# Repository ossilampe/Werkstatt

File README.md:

# Werkstatt

Eigene Geräte und Platinen für die Werkstatt, mit Schaltplan, Platinendaten und Firmware.

| Projekt | Hardware | Wofür | Stand |
|---|---|---|---|
| [T12-Station-2-Kolben](T12-Station-2-Kolben) | Waveshare ESP32-S3 Touch-LCD 3,5″ + 2 × fertige T12-Steuerplatine (STM32 Ver21S) mit eigener UART-Firmware | Lötstation für 2 T12-Kolben: Touch + Drehgeber, Spitzenprofile aus Home Assistant, Sprachausgabe, Lüfter, Absaugung | läuft im 3D-Druck-Gehäuse (mit 1 Modul getestet), Absaugung folgt |
| [T12-Station-1-Kolben](T12-Station-1-Kolben) | wie oben, 1 × T12-Steuerplatine | dieselbe Station für einen Kolben | Konfiguration fertig, Gehäuse wie 2 Kolben |
| [T12-Loetstation](T12-Loetstation) | Waveshare ESP32-S3 Touch-LCD 3,5″ + eigene Platine (KiCad, JLCPCB) | erster Entwurf mit eigener Platine für 2 Kolben | Platine v1.1 fertig, pausiert |
| [E-Last-ZHIYU-ESP32](E-Last-ZHIYU-ESP32) | Elektronische Last ZHIYU ZPB30A1 (60 W) mit freier Firmware + Waveshare ESP32-S3 Touch-LCD 3,5″ | Last per Display und Home Assistant steuern; geplant: Akkutest, Rampentest mit Protokoll | geflasht, Display zeigt Live-Daten; Befehle und Kalibrierung offen |
| [Labornetzteil-XY6020L](Labornetzteil-XY6020L) | 60-V/20-A-Netzteil + XY6020L (Modbus) + Waveshare ESP32-S3 Touch-LCD 3,5″ | Labornetzteil 0–60 V / 0–20 A mit Touch, Schutzgrenzen, Home Assistant | Entwurf: Konfiguration v1 geschrieben, noch nicht aufgebaut |
| [Mikroskop](Mikroskop) | Raspberry Pi 4 + HQ-Kamera + offizielles 7″-Touchdisplay + 4 Taster | Digitales Mikroskop: Zoom bis 8×, Verschieben per Wischen, Bild-Einstellungen, Foto auf SMB-Freigabe | App geschrieben, auf echter Hardware noch nicht getestet |

**Gehäuse der T12-Station zum Drucken:** [MakerWorld](https://makerworld.com/de/models/3663781-t12-lotstation-esp32-s3-touch-display-2-kolben)

**Hinweis:** WLAN-Daten und Passwörter kommen per `!secret` aus der eigenen `secrets.yaml`. Eine Vorlage liegt jeweils als `secrets.yaml.example` im Projektordner.

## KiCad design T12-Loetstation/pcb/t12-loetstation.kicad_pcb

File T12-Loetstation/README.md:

# T12 Lötstation – 2 Kolben gleichzeitig

Selbstgebaute Lötstation für **zwei T12-Lötspitzen gleichzeitig**, mit eigenem Touch-Display, Drehgeber, Lüftersteuerung, Anschluss für eine Lötrauch-Absaugung und Sprachausgabe.

> **Stand 13.11.2026: pausiert.** Die Platine (v1.1) ist fertig geprüft und bei JLCPCB bestellbar, aber noch nicht bestellt. Die Firmware ist ein Entwurf (noch nicht kompiliert, Lüfter/Absaugung/Ton fehlen).

## So soll es aussehen

Display: Waveshare ESP32-S3-Touch-LCD-3.5 quer (480 × 320), ESPHome + LVGL. Bedienung per Touch oder Drehgeber (drehen = Temperatur, langer Druck = Menü).

| | |
|---|---|
|  |  |
|  |  |
|  |  |
|  | |

Die Bilder werden mit [`docs/gen_menues.py`](docs/gen_menues.py) erzeugt (Maße und Farben wie in der Firmware). „Geplant“ heißt: in der Firmware noch nicht umgesetzt.

**Zustände pro Kolben:** AUS · HEIZT (orange) · BEREIT (grün) · KÜHLT AB · STANDBY (blau, Kolben in der Ablage) · SCHLÄFT · KEINE SPITZE (gelb) · Fehler Übertemperatur / heizt nicht / Messung (rot).

## Funktionen

- 2 × T12 an 24 V (je ca. 70 W), jede Spitze eigene Solltemperatur, Festwerte 280 / 330 / 380 °C
- Temperaturmessung im Heizpausen-Fenster: Auto-Zero-Verstärker MCP6V27 (× 221) → 16-Bit-ADC ADS1115, Kaltstelle MCP9700
- Standby und Schlafen über den Neigungsschalter im Griff, Erkennung „keine Spitze“
- Nach Stromausfall bleiben beide Kolben **aus**
- Netzteil-Lüfter 12 V, temperaturgeregelt über DS18B20
- Buchse vorne (Cinch) für eine 12-V-Absaugung: Drehzahl am Display, schaltet sich ein, wenn ein Kolben in die Hand genommen wird, 10 s Nachlauf
- Pieptöne und deutsche Sprachansagen über den Lautsprecher des Displays (ES8311)

## Hardware

| Teil | |
|---|---|
| Display | Waveshare ESP32-S3-Touch-LCD-3.5 |
| Netzteil | 24 V / 10 A |
| Spannungen | 2 × LM2596-Modul (5 V Display, 12 V Lüfter) per Kabel, AMS1117-3.3 für die Analogseite |
| Heizung | IRF5305 (P-Kanal, Plus-Seite) mit MMBT3904-Treiber, je Kolben eine Sicherung im Gehäuse |
| Bedienung | Drehgeber ALPS STEC12E08 |
| Lüfter | 2 × AO3400A mit 25 kHz PWM |

### GPIO-Belegung (Stiftleiste des Displays)

| GPIO | Funktion | | GPIO | Funktion |
|---|---|---|---|---|
| 38 | Heizung A | | 17 | Griffschalter A |
| 39 | Heizung B | | 18 | Griffschalter B |
| 40 / 41 | Drehgeber A / B | | 21 | DS18B20 |
| 42 | Drehgeber Taster | | 47 | Netzteil-Lüfter (PWM) |
| 8 / 7 | I²C SDA / SCL (ADS1115 0x48) | | 48 | Absaugung (PWM) |

## Platine

150 × 105 mm, 2 Lagen, vollständig bedruckt. Alle Klemmen und Buchsen sind mit Signal und GPIO beschriftet.

- **Schaltplan:** [pcb/t12-schaltplan.pdf](pcb/t12-schaltplan.pdf)
- **KiCad 10:** `pcb/t12-loetstation.kicad_pro`
- **Bestellung bei JLCPCB:** [pcb/jlc/ANLEITUNG.md](pcb/jlc/ANLEITUNG.md)
  - Gerber, Stückliste mit LCSC-Nummern (21 Positionen, nur SMD) und Bestückungsdatei liegen bereit.
  - Die Drehungen sind in der JLC-Vorschau kontrolliert.
- **Selbst löten:** die bedrahteten Teile ([pcb/jlc/Selbst_loeten.csv](pcb/jlc/Selbst_loeten.csv)): Schraubklemmen, JST-XH-Buchsen, IRF5305, Elkos, MCP9700, Sicherungshalter.

Die Platine wird komplett aus Python erzeugt (mit dem Python von KiCad aufrufen, im Ordner `pcb`):

```
design.py    Bauteile und Netze (eine Quelle für alles)
gen_sch.py   -> Schaltplan
gen_pcb.py   -> Platzierung, Bedruckung, Leiterbahnklassen
route.py     -> Freerouting (export / run / import), Masseflächen
make_jlc.py  -> Gerber-Zip, BOM, CPL für JLCPCB
```

### Änderungen v1.1 (Durchsicht vor der Bestellung)
- 1-MΩ-Pull-up (Erkennung „keine Spitze“) an die Spitze verlegt. Vorher hätte er den Messverstärker übersteuert.
- Filter am Messeingang 10 nF → 1 nF: schwingt nach dem Abschalten der Heizung in unter 1 ms ein.
- Massepads der Klemmen J1–J3 vollflächig an die Massefläche (2 × 3 A Heizstrom).
- Drehung der SS14-Dioden in der Bestückungsdatei korrigiert.

## Firmware

[`firmware/t12-loetstation.yaml`](firmware/t12-loetstation.yaml) + [`firmware/t12/loet.h`](firmware/t12/loet.h) (Regler, Zustände).

- **Regelung:** alle 100 ms. Beide Heizungen kurz aus, 3 ms warten, ADS1115 lesen, dann PI-Regler je Kolben.
- **Sicherheit:** über 480 °C, Spitze fehlt oder kein Temperaturanstieg in 20 s → Heizung aus.
- **WLAN-Daten:** per `!secret`, Vorlage in [`firmware/secrets.yaml.example`](firmware/secrets.yaml.example).

**Offen:**
- Lüfter, DS18B20, Absaugung
- Ton und Sprachausgabe
- Menüseiten 03, 05, 06
- Schalter auf `ALWAYS_OFF`
- Kalibrierung mit Spitzenthermometer
- Griffbelegung und Neigungsschalter nachmessen

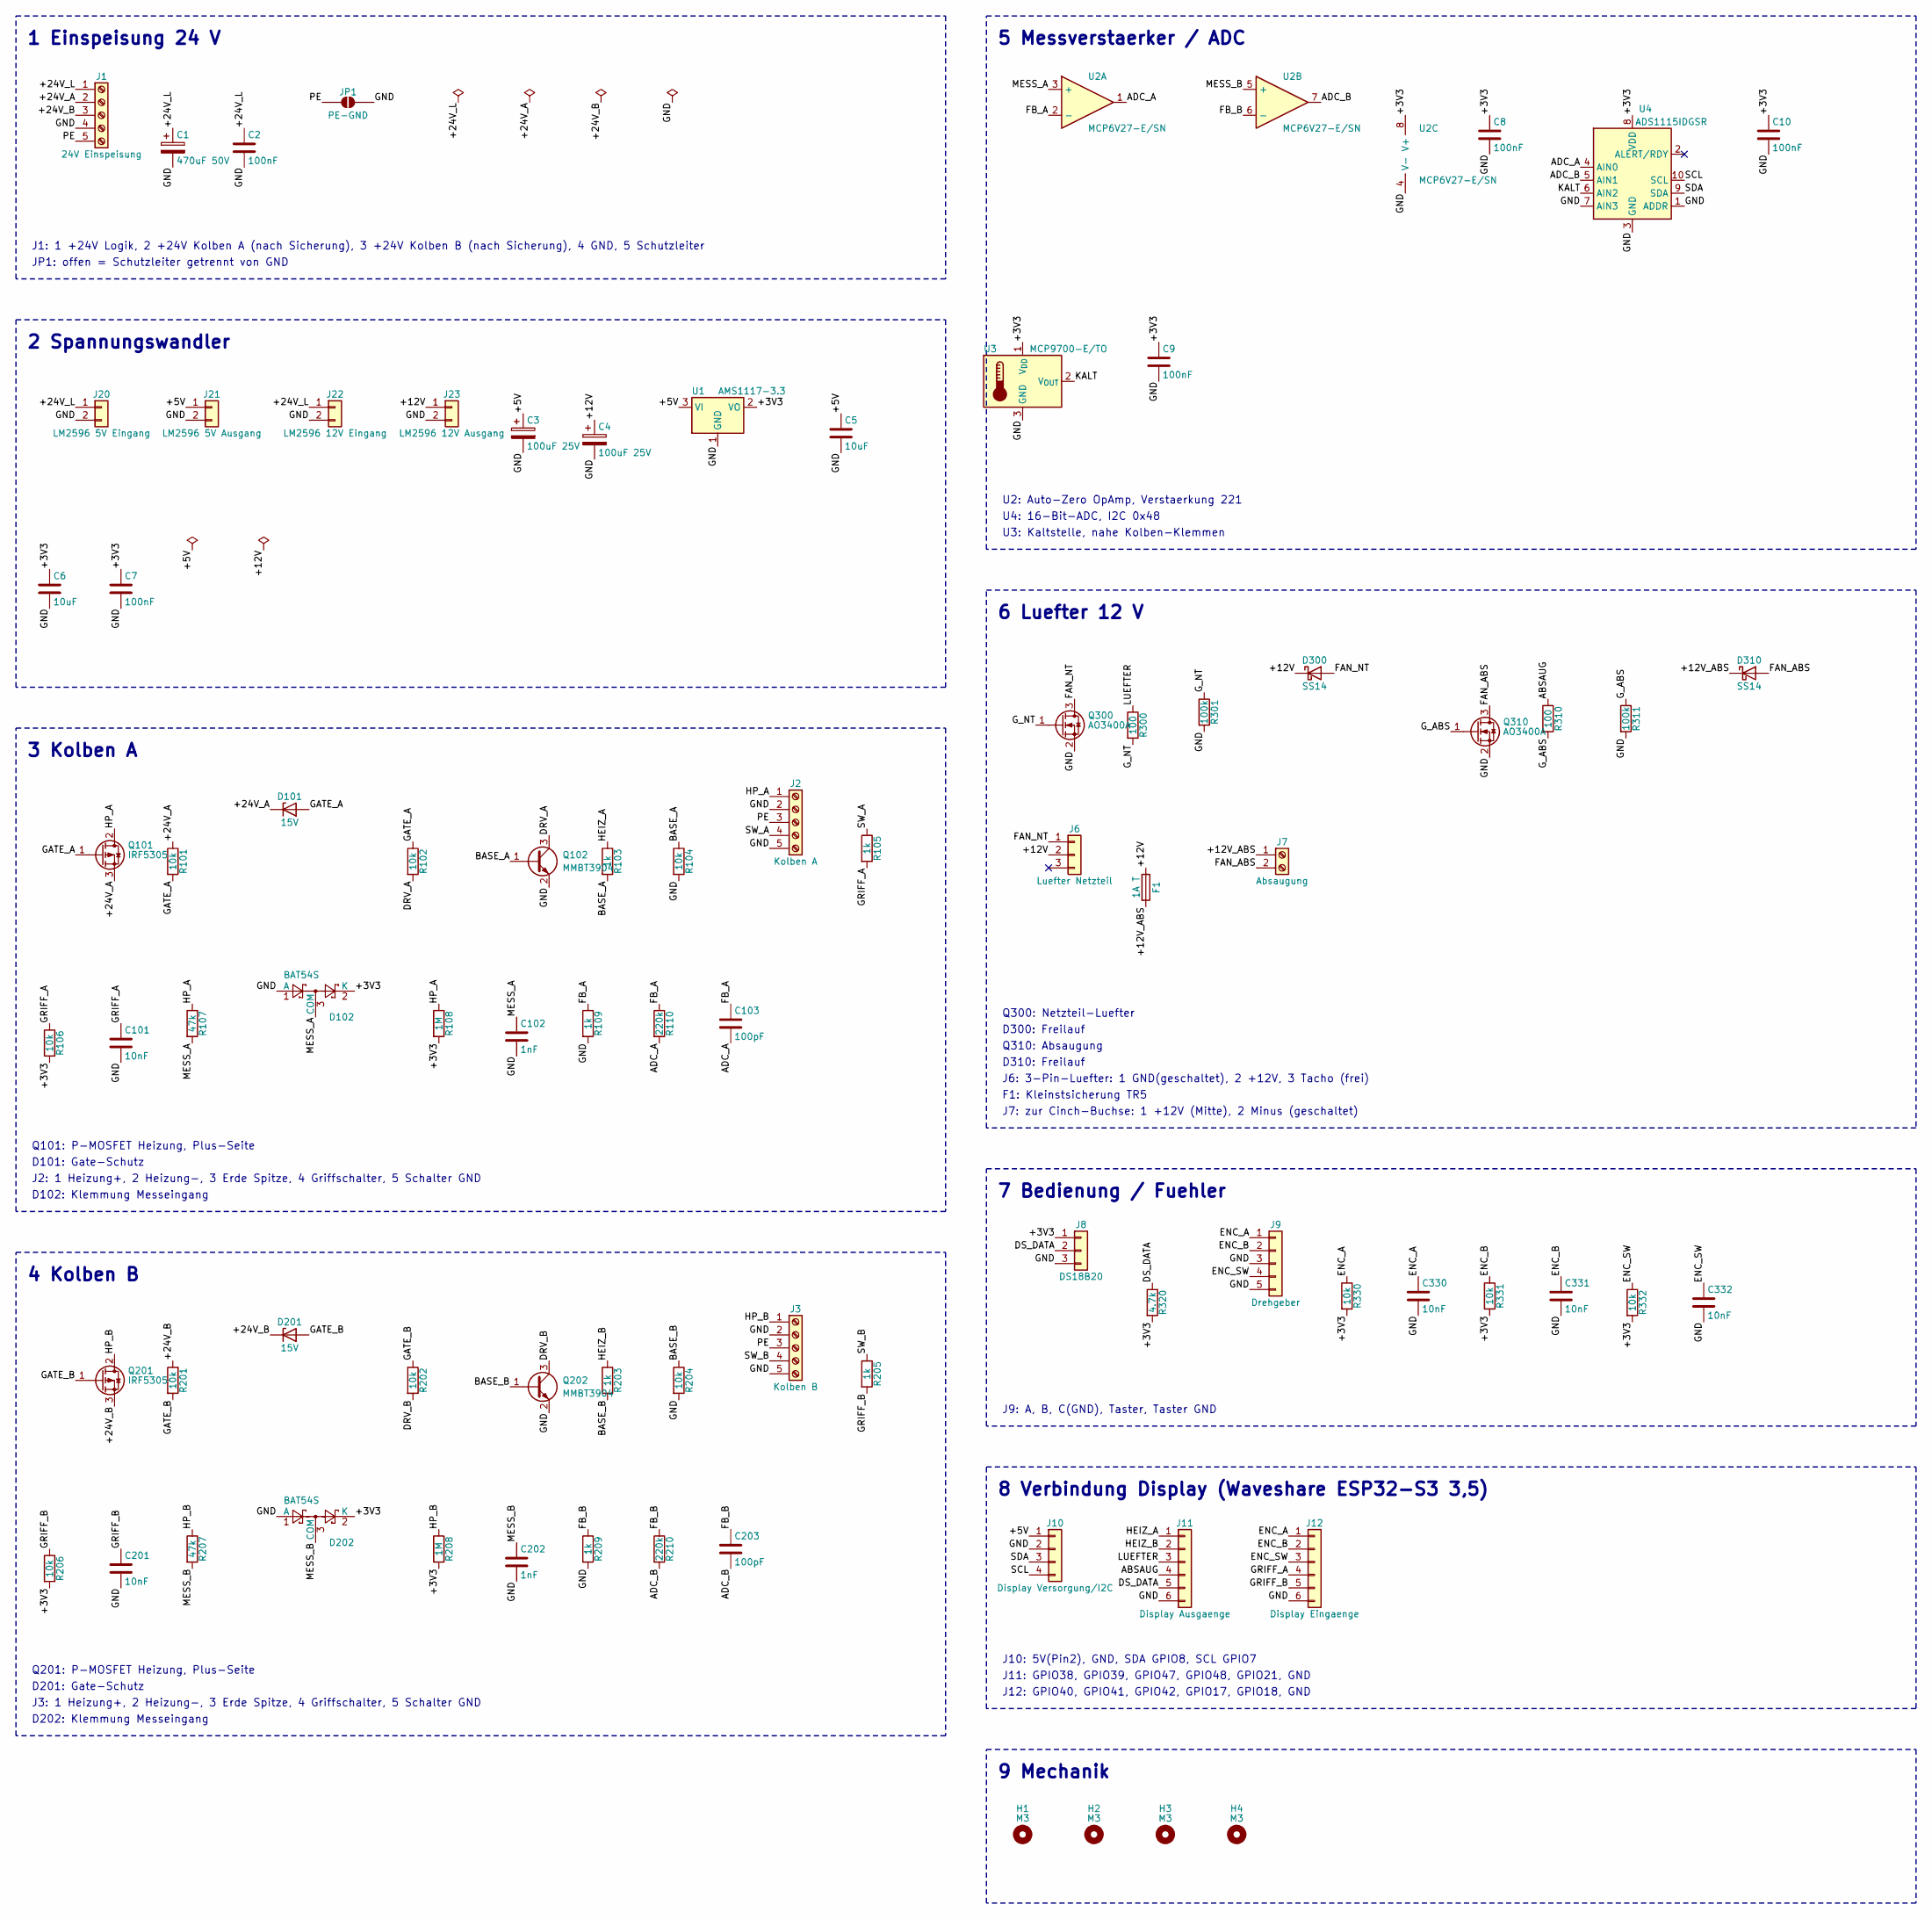
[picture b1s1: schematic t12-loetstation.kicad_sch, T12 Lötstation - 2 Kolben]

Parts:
C1: 470uF 50V; CP_Radial_D10.0mm_P5.00mm
C2, C7, C8, C9, C10: 100nF; C_0805_2012Metric; LCSC C49678
C3, C4: 100uF 25V; CP_Radial_D6.3mm_P2.50mm
C5, C6: 10uF; C_0805_2012Metric; LCSC C15850
C101, C201, C330, C331, C332: 10nF; C_0805_2012Metric; LCSC C1710
C102, C202: 1nF; C_0805_2012Metric; LCSC C46653
C103, C203: 100pF; C_0805_2012Metric; LCSC C1790
D101, D201: 15V; D_MiniMELF; LCSC C181074
D102, D202: BAT54S; SOT-23; LCSC C47546
D300, D310: SS14; D_SMA; LCSC C2480
F1: 1A T; Fuseholder_TR5_Littelfuse_No560_No460
H1, H2, H3, H4: M3; MountingHole_3.2mm_M3
J1: 24V Einspeisung; TerminalBlock_Phoenix_MKDS-1,5-5-5.08_1x05_P5.08mm_Horizont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; LCSC C42377750
J2: Kolben A; TerminalBlock_Phoenix_MKDS-1,5-5-5.08_1x05_P5.08mm_Horizont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; LCSC C42377750
J3: Kolben B; TerminalBlock_Phoenix_MKDS-1,5-5-5.08_1x05_P5.08mm_Horizont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; LCSC C42377750
J6: Luefter Netzteil; Molex_KK-254_AE-6410-03A_1x03_P2.54mm_Vertical
J7: Absaugung; TerminalBlock_Phoenix_MKDS-1,5-2-5.08_1x02_P5.08mm_Horizont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; LCSC C8465
J8: DS18B20; JST_XH_B3B-XH-A_1x03_P2.50mm_Vertical; LCSC C144394
J9: Drehgeber; JST_XH_B5B-XH-A_1x05_P2.50mm_Vertical; LCSC C157991
J10: Display Versorgung/I2C; JST_XH_B4B-XH-A_1x04_P2.50mm_Vertical; LCSC C144395
J11: Display Ausgaenge; JST_XH_B6B-XH-A_1x06_P2.50mm_Vertical; LCSC C144397
J12: Display Eingaenge; JST_XH_B6B-XH-A_1x06_P2.50mm_Vertical; LCSC C144397
J20: LM2596 5V Eingang; SolderWire-0.5sqmm_1x02_P4.6mm_D0.9mm_OD2.1mm
J21: LM2596 5V Ausgang; SolderWire-0.5sqmm_1x02_P4.6mm_D0.9mm_OD2.1mm
J22: LM2596 12V Eingang; SolderWire-0.5sqmm_1x02_P4.6mm_D0.9mm_OD2.1mm
J23: LM2596 12V Ausgang; SolderWire-0.5sqmm_1x02_P4.6mm_D0.9mm_OD2.1mm
JP1: PE-GND; SolderJumper-2_P1.3mm_Open_RoundedPad1.0x1.5mm
Q101, Q201: IRF5305; TO-220-3_Vertical
Q102, Q202: MMBT3904; SOT-23; LCSC C20526
Q300, Q310: AO3400A; SOT-23; LCSC C20917
R101, R102, R104, R106, R201, R202, R204, R206, R330, R331, R332: 10k; R_0805_2012Metric; LCSC C17414
R103, R105, R109, R203, R205, R209: 1k; R_0805_2012Metric; LCSC C17513
R107, R207: 47k; R_0805_2012Metric; LCSC C17713
R108, R208: 1M; R_0805_2012Metric; LCSC C17514
R110, R210: 220k; R_0805_2012Metric; LCSC C17556
R300, R310: 100; R_0805_2012Metric; LCSC C17408
R301, R311: 100k; R_0805_2012Metric; LCSC C149504
R320: 4.7k; R_0805_2012Metric; LCSC C17673
U1: AMS1117-3.3; SOT-223-3_TabPin2; LCSC C6186
U2: MCP6V27-E/SN; SOIC-8_3.9x4.9mm_P1.27mm; LCSC C636392
U3: MCP9700-E/TO; TO-92_Inline_Wide
U4: ADS1115IDGSR; TSSOP-10_3x3mm_P0.5mm; LCSC C37593

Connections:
+3V3: C6.1, C7.1, C8.1, C9.1, C10.1, D102.2 (K), D202.2 (K), J8.1, R106.2, R108.2, R206.2, R208.2, R320.2, R330.2, R331.2, R332.2, U1.2 (VO), U2.8 (V+), U3.1 (V_{DD}), U4.8 (VDD)
+5V: C3.1, C5.1, J10.1, J21.1, U1.3 (VI)
+12V: C4.1, D300.1 (K), F1.1, J6.2, J23.1
+12V_ABS: D310.1 (K), F1.2, J7.1
+24V_A: D101.1 (K), J1.2, Q101.3 (S), R101.1
+24V_B: D201.1 (K), J1.3, Q201.3 (S), R201.1
+24V_L: C1.1, C2.1, J1.1, J20.1, J22.1
ABSAUG: J11.4, R310.1
ADC_A: C103.2, R110.2, U2.1, U4.4 (AIN0)
ADC_B: C203.2, R210.2, U2.7, U4.5 (AIN1)
BASE_A: Q102.1 (B), R103.2, R104.1
BASE_B: Q202.1 (B), R203.2, R204.1
DRV_A: Q102.3 (C), R102.2
DRV_B: Q202.3 (C), R202.2
DS_DATA: J8.2, J11.5, R320.1
ENC_A: C330.1, J9.1, J12.1, R330.1
ENC_B: C331.1, J9.2, J12.2, R331.1
ENC_SW: C332.1, J9.4, J12.3, R332.1
FAN_ABS: D310.2 (A), J7.2, Q310.3 (D)
FAN_NT: D300.2 (A), J6.1, Q300.3 (D)
FB_A: C103.1, R109.1, R110.1, U2.2 (-)
FB_B: C203.1, R209.1, R210.1, U2.6 (-)
GATE_A: D101.2 (A), Q101.1 (G), R101.2, R102.1
GATE_B: D201.2 (A), Q201.1 (G), R201.2, R202.1
GND: C1.2, C2.2, C3.2, C4.2, C5.2, C6.2, C7.2, C8.2, C9.2, C10.2, C101.2, C102.2, C201.2, C202.2, C330.2, C331.2, C332.2, D102.1 (A), D202.1 (A), J1.4, J2.2, J2.5, J3.2, J3.5, J8.3, J9.3, J9.5, J10.2, J11.6, J12.6, J20.2, J21.2, J22.2, J23.2, JP1.2 (B), Q102.2 (E), Q202.2 (E), Q300.2 (S), Q310.2 (S), R104.2, R109.2, R204.2, R209.2, R301.2, R311.2, U1.1 (GND), U2.4 (V-), U3.3 (GND), U4.1 (ADDR), U4.3 (GND), U4.7 (AIN3)
GRIFF_A: C101.1, J12.4, R105.2, R106.1
GRIFF_B: C201.1, J12.5, R205.2, R206.1
G_ABS: Q310.1 (G), R310.2, R311.1
G_NT: Q300.1 (G), R300.2, R301.1
HEIZ_A: J11.1, R103.1
HEIZ_B: J11.2, R203.1
HP_A: J2.1, Q101.2 (D), R107.1, R108.1
HP_B: J3.1, Q201.2 (D), R207.1, R208.1
KALT: U3.2 (V_{OUT}), U4.6 (AIN2)
LUEFTER: J11.3, R300.1
MESS_A: C102.1, D102.3 (COM), R107.2, U2.3 (+)
MESS_B: C202.1, D202.3 (COM), R207.2, U2.5 (+)
PE: J1.5, J2.3, J3.3, JP1.1 (A)
SCL: J10.4, U4.10 (SCL)
SDA: J10.3, U4.9 (SDA)
SW_A: J2.4, R105.1
SW_B: J3.4, R205.1

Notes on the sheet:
1 Einspeisung 24 V
J1: 1 +24V Logik, 2 +24V Kolben A (nach Sicherung), 3 +24V Kolben B (nach Sicherung), 4 GND, 5 Schutzleiter
JP1: offen = Schutzleiter getrennt von GND
2 Spannungswandler
3 Kolben A
Q101: P-MOSFET Heizung, Plus-Seite
D101: Gate-Schutz
J2: 1 Heizung+, 2 Heizung-, 3 Erde Spitze, 4 Griffschalter, 5 Schalter GND
D102: Klemmung Messeingang
4 Kolben B
Q201: P-MOSFET Heizung, Plus-Seite
D201: Gate-Schutz
J3: 1 Heizung+, 2 Heizung-, 3 Erde Spitze, 4 Griffschalter, 5 Schalter GND
D202: Klemmung Messeingang
5 Messverstaerker / ADC
U2: Auto-Zero OpAmp, Verstaerkung 221
U4: 16-Bit-ADC, I2C 0x48
U3: Kaltstelle, nahe Kolben-Klemmen
6 Luefter 12 V
Q300: Netzteil-Luefter
D300: Freilauf
Q310: Absaugung
D310: Freilauf
J6: 3-Pin-Luefter: 1 GND(geschaltet), 2 +12V, 3 Tacho (frei)
F1: Kleinstsicherung TR5
J7: zur Cinch-Buchse: 1 +12V (Mitte), 2 Minus (geschaltet)
7 Bedienung / Fuehler
J9: A, B, C(GND), Taster, Taster GND
8 Verbindung Display (Waveshare ESP32-S3 3,5)
J10: 5V(Pin2), GND, SDA GPIO8, SCL GPIO7
J11: GPIO38, GPIO39, GPIO47, GPIO48, GPIO21, GND
J12: GPIO40, GPIO41, GPIO42, GPIO17, GPIO18, GND
9 Mechanik

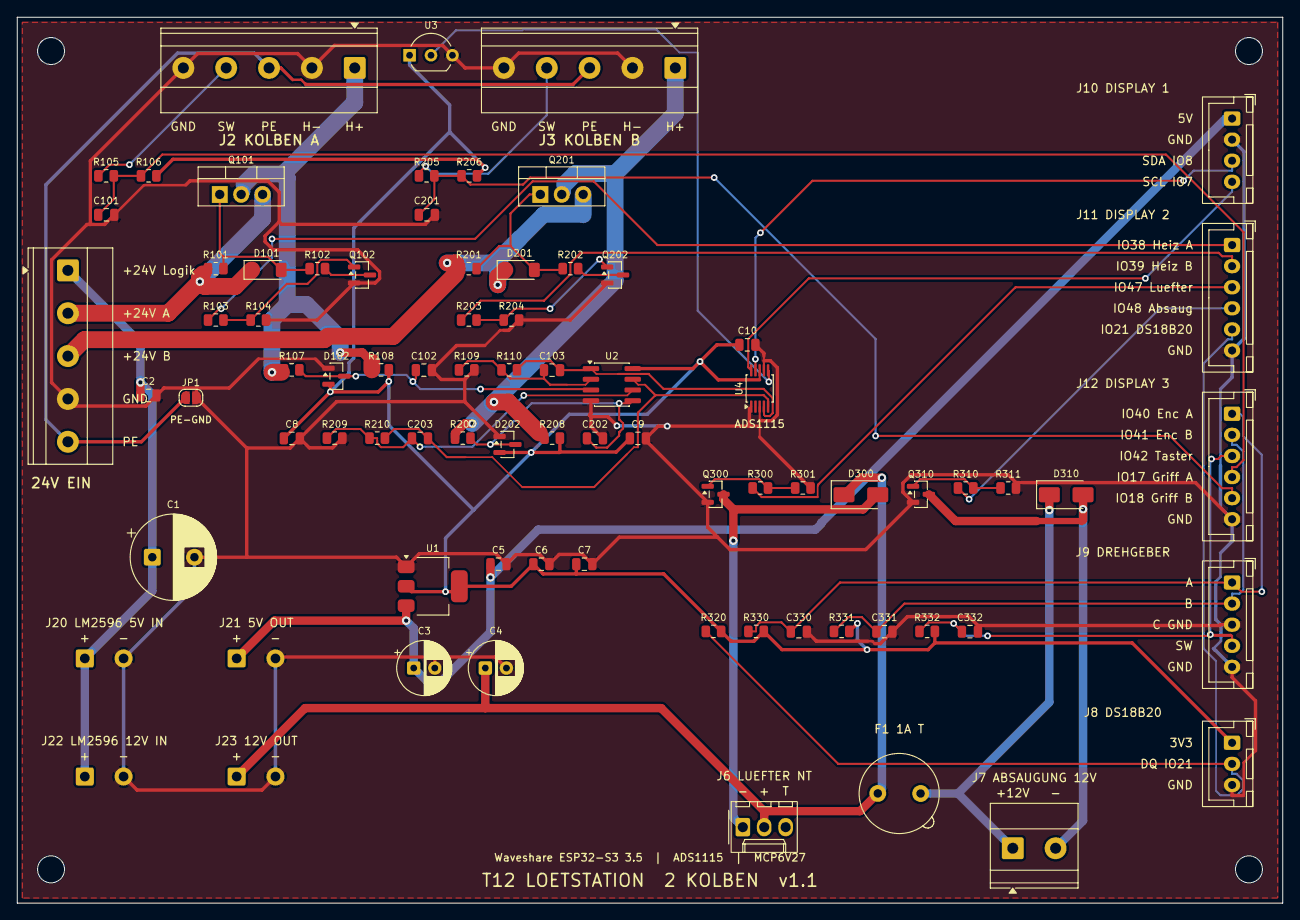
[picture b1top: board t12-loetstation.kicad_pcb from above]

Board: 2 copper layers, 150.0 x 105.0 mm, 83 parts (0 on the bottom side), 42 nets.

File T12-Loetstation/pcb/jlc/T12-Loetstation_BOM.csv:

Comment,Designator,Footprint,LCSC Part #
100nF,"C10,C2,C7,C8,C9",C_0805_2012Metric,C49678
10nF,"C101,C201,C330,C331,C332",C_0805_2012Metric,C1710
1nF,"C102,C202",C_0805_2012Metric,C46653
100pF,"C103,C203",C_0805_2012Metric,C1790
10uF,"C5,C6",C_0805_2012Metric,C15850
15V,"D101,D201",D_MiniMELF,C181074
BAT54S,"D102,D202",SOT-23,C47546
SS14,"D300,D310",D_SMA,C2480
MMBT3904,"Q102,Q202",SOT-23,C20526
AO3400A,"Q300,Q310",SOT-23,C20917
10k,"R101,R102,R104,R106,R201,R202,R204,R206,R330,R331,R332",R_0805_2012Metric,C17414
1k,"R103,R105,R109,R203,R205,R209",R_0805_2012Metric,C17513
47k,"R107,R207",R_0805_2012Metric,C17713
1M,"R108,R208",R_0805_2012Metric,C17514
220k,"R110,R210",R_0805_2012Metric,C17556
100,"R300,R310",R_0805_2012Metric,C17408
100k,"R301,R311",R_0805_2012Metric,C149504
4.7k,R320,R_0805_2012Metric,C17673
AMS1117-3.3,U1,SOT-223-3_TabPin2,C6186
MCP6V27-E/SN,U2,SOIC-8_3.9x4.9mm_P1.27mm,C636392
ADS1115IDGSR,U4,TSSOP-10_3x3mm_P0.5mm,C37593

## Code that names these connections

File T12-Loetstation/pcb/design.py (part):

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
# ------------------------------------------------------------------ Luefter
B = "6 Luefter 12 V"
for k, n, gpio, desc in (("NT", 300, "LUEFTER", "Netzteil-Luefter"), ("ABS", 310, "ABSAUG", "Absaugung")):
    part("Q%d" % n, "Transistor_FET:Q_NMOS_GSD", "AO3400A", SOT23,
         {"1": "G_" + k, "2": "GND", "3": "FAN_" + k}, B, lcsc="C20917", desc=desc)
    R("R%d" % n, "100", gpio, "G_" + k, B, "C17408")
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    part("D%d" % n, "Device:D_Schottky", "SS14", "Diode_SMD:D_SMA",
         {"1": "+12V" if k == "NT" else "+12V_ABS", "2": "FAN_" + k}, B, lcsc="C2480", desc="Freilauf")
part("J6", "Connector_Generic:Conn_01x03", "Luefter Netzteil", "Connector_Molex:Molex_KK-254_AE-6410-03A_1x03_P2.54mm_Vertical",
     {"1": "FAN_NT", "2": "+12V", "3": None}, B, desc="3-Pin-Luefter: 1 GND(geschaltet), 2 +12V, 3 Tacho (frei)")
part("F1", "Device:Fuse", "1A T", "Fuse:Fuseholder_TR5_Littelfuse_No560_No460",
     {"1": "+12V", "2": "+12V_ABS"}, B, desc="Kleinstsicherung TR5")
part("J7", "Connector:Screw_Terminal_01x02", "Absaugung", TB % (2, 2),
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    part("H%d" % i, "Mechanical:MountingHole", "M3", "MountingHole:MountingHole_3.2mm_M3", {}, "9 Mechanik")

# Netz -> Display-Signalnamen fuer Bedruckung
GPIO = {"HEIZ_A": "IO38", "HEIZ_B": "IO39", "LUEFTER": "IO47", "ABSAUG": "IO48", "DS_DATA": "IO21",
        "ENC_A": "IO40", "ENC_B": "IO41", "ENC_SW": "IO42", "GRIFF_A": "IO17", "GRIFF_B": "IO18",
        "SDA": "IO8", "SCL": "IO7"}

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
